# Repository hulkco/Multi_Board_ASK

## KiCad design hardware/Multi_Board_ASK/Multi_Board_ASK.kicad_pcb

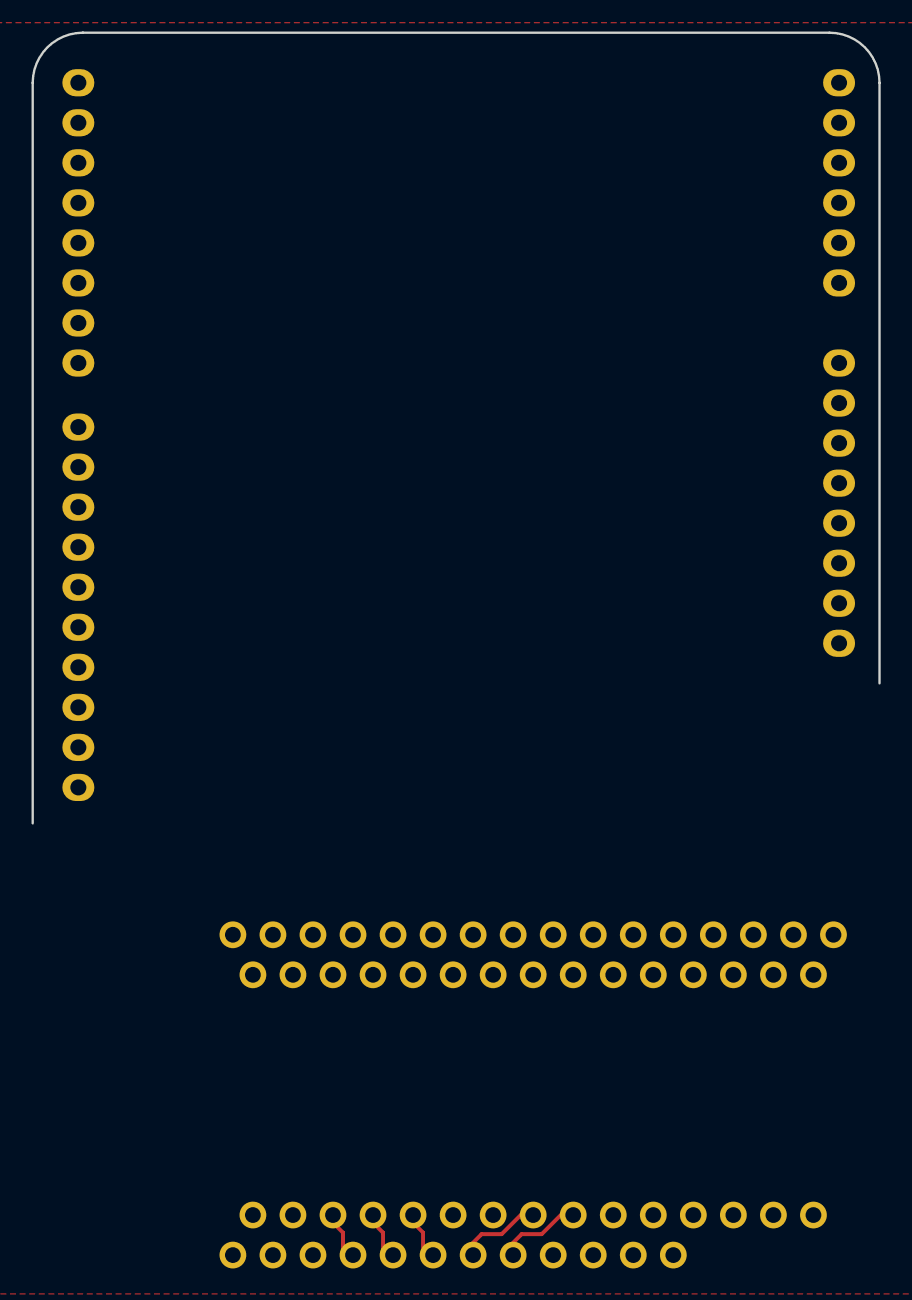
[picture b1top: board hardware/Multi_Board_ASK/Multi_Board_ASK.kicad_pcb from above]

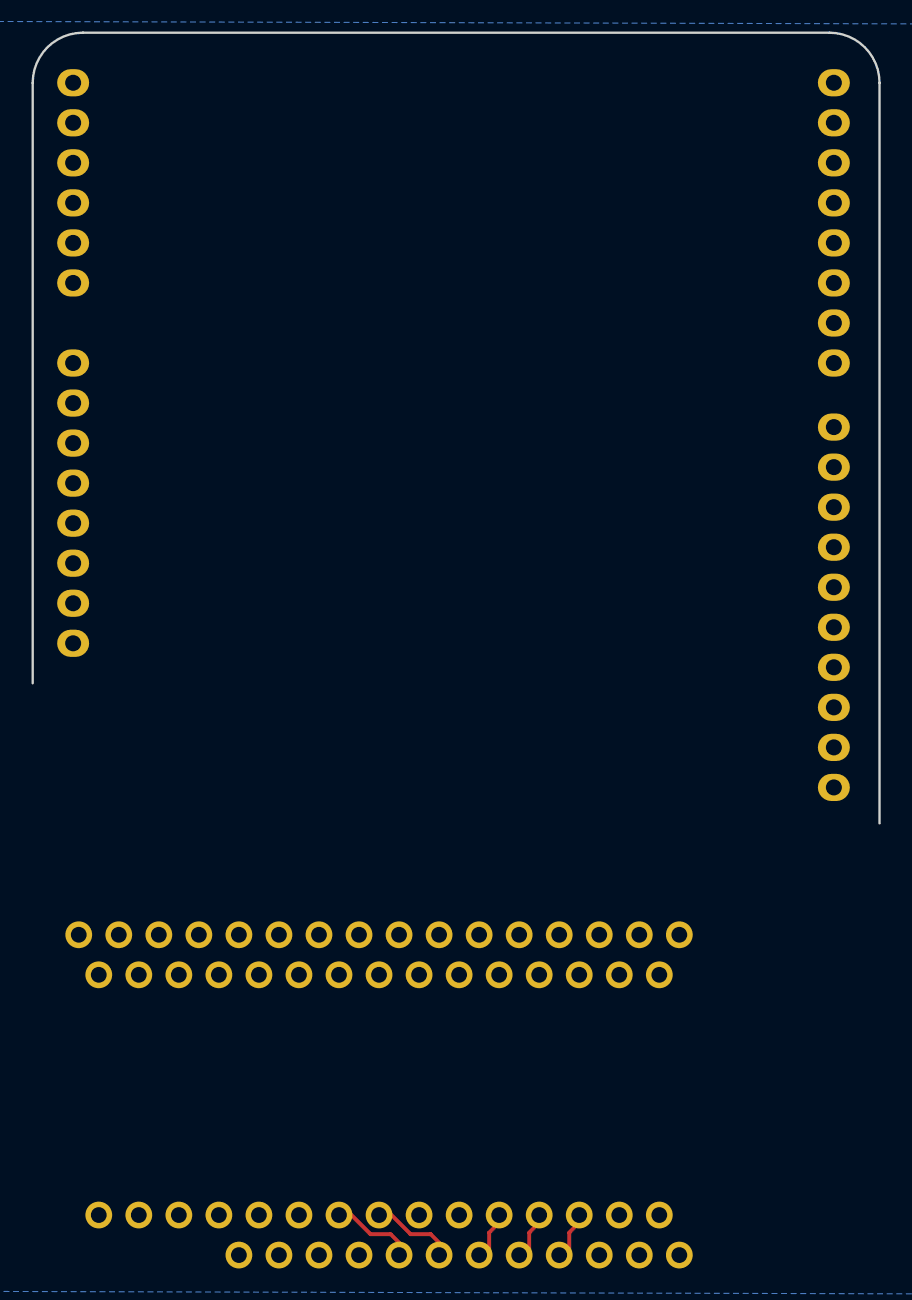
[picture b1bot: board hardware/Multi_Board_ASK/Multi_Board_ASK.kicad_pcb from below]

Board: 2 copper layers, 8 parts (2 on the bottom side), 27 nets.

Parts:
J1: feather long; PinHeader_1x16_P2.54mm_Vertical
J2: feather short; PinHeader_1x12_P2.54mm_Vertical
J3, J4: Conn_01x15; PinSocket_1x15_P2.54mm_Vertical
P1: Power; Socket_Strip_Arduino_1x08
P2: Analog; Socket_Strip_Arduino_1x06
P3: Digital; Socket_Strip_Arduino_1x10
P4: Digital; Socket_Strip_Arduino_1x08

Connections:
+3V3: J1.15, J4.14, P1.4
+5V: J2.10, J4.4, P1.5
/0(Rx): J1.3, J3.2, P4.8
/1(Tx): J1.2, J3.1, P4.7
/A0: J1.12, J4.12, P2.1
/A1: J1.11, J4.11, P2.2
/A2: J1.10, J4.10, P2.3
/A3: J1.9, J4.9, P2.4
/A6: J1.8, J4.6
/A7: J1.7, J4.5
/D2: J1.1, J3.5, P4.6
/D3(**): J2.3, J3.6, P4.5
/D4: J2.4, J3.7, P4.4
/D5(**): J2.5, J3.8, P4.3
/D6(**): J2.6, J3.9, P4.2
/D7: J3.10, P4.1
/D8: J2.7, J3.11, P3.10
/D9(**): J2.8, J3.12, P3.9
/D10(**): J2.9, J3.13, P3.8
/D11-MOSI: J1.5, J3.14, P3.7
/D12-MISO: J1.4, J3.15, P3.6
/D13-SCK: J1.6, J4.15, P3.5
/SCL-A5: J2.2, J4.7, P2.6, P3.1
/SDA-A4: J2.1, J4.8, P2.5, P3.2
/VIN: J2.12, J4.1, P1.8
/~RESET: J1.16, J3.3, J4.3, P1.3
GND: J1.13, J3.4, J4.2, P1.6, P1.7, P3.4

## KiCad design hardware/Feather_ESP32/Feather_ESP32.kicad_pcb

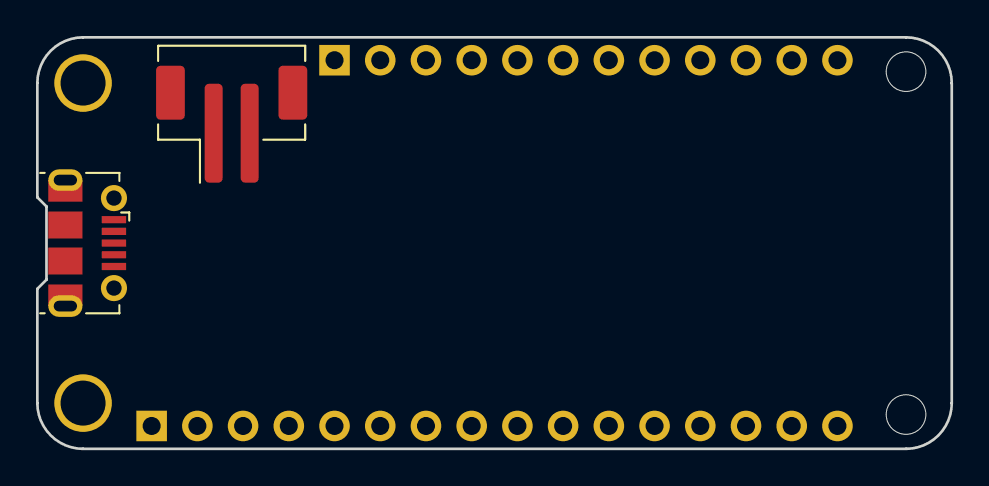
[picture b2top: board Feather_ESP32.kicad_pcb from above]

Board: 2 copper layers, 50.8 x 22.9 mm, 4 parts (0 on the bottom side), 3 nets, no tracks yet.

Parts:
J1: Conn_Battery; JST_PH_B2B-PH-SM4-TB_1x02-1MP_P2.00mm_Vertical
J2: USB_B_Micro; USB_Micro-B_Molex-105017-0001
J3: Conn_Left; PinSocket_1x16_P2.54mm_Vertical
J4: Conn_Right; PinSocket_1x12_P2.54mm_Vertical

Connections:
+BATT: J1.2, J4.1
GND: J1.1, J2.5, J2.6, J3.4
VBUS: J2.1, J4.3

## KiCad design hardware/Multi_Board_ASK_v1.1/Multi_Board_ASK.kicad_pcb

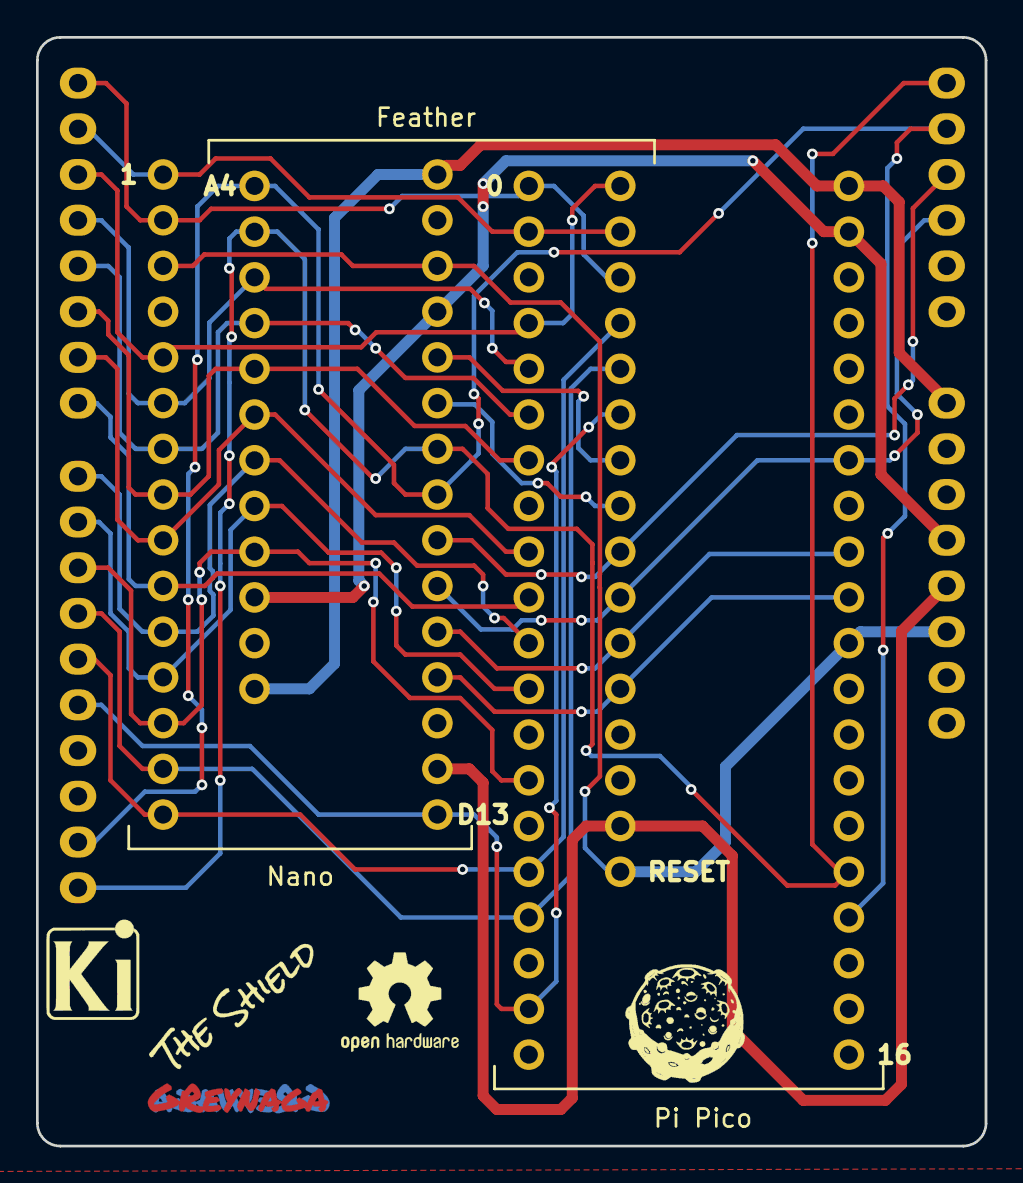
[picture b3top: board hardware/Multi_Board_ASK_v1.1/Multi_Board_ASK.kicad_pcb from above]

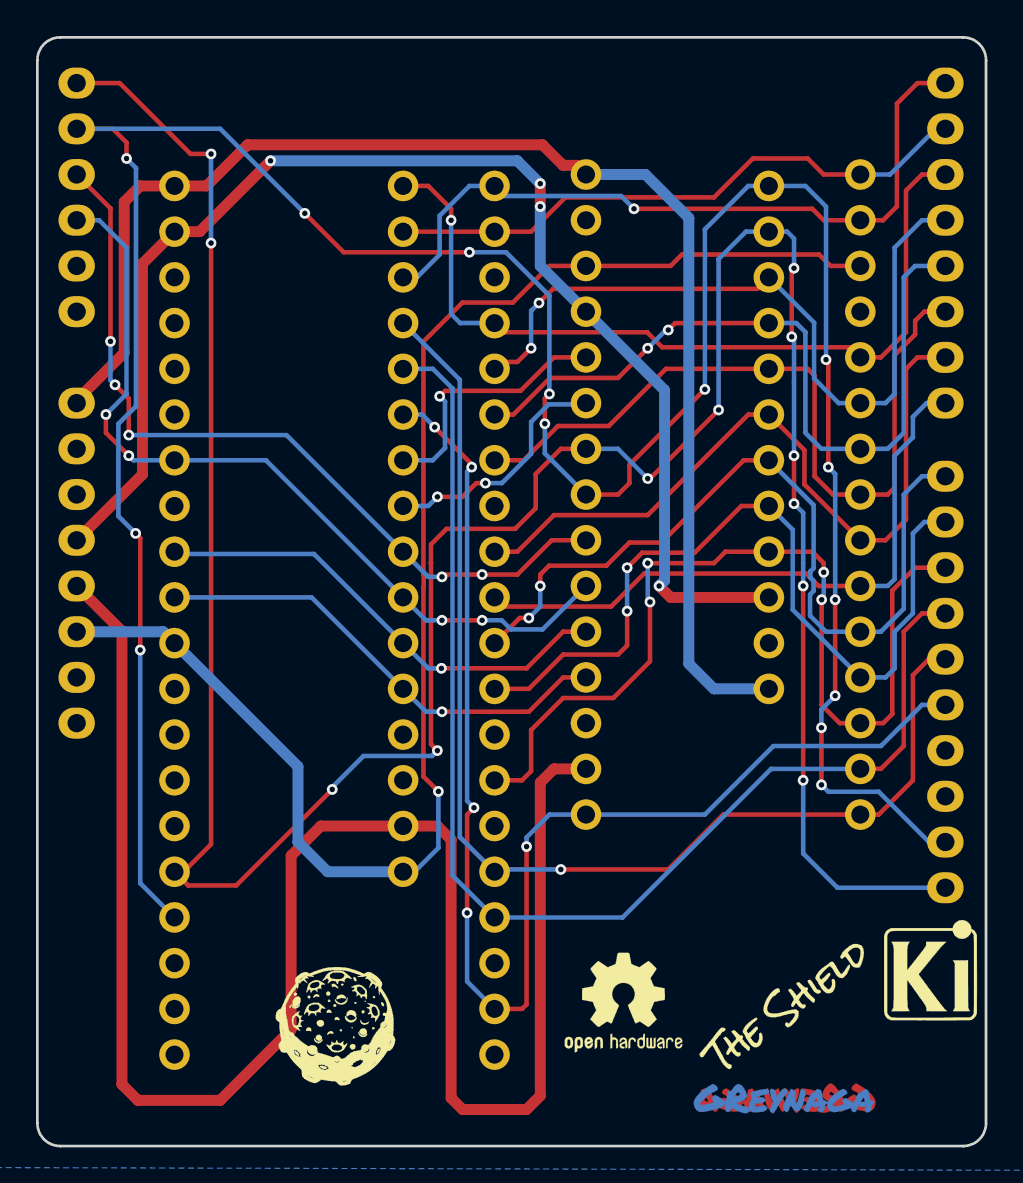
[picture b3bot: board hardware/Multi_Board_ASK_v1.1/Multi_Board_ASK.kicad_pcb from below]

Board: 2 copper layers, 52.7 x 61.6 mm, 20 parts (5 on the bottom side), 27 nets.

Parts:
J1: feather long; PinSocket_1x16_P2.54mm_Vertical
J2: feather short; PinSocket_1x12_P2.54mm_Vertical
J3: Nano 2; PinSocket_1x15_P2.54mm_Vertical
J4: Nano 1; PinSocket_1x15_P2.54mm_Vertical
J5: Pico 1; PinSocket_1x20_P2.54mm_Vertical
J6: Pico 2; PinSocket_1x20_P2.54mm_Vertical
P1: Power; Socket_Strip_Arduino_1x08
P2: Analog; Socket_Strip_Arduino_1x06
P3: Digital; Socket_Strip_Arduino_1x10
P4: Digital; Socket_Strip_Arduino_1x08
U1, U7: Feather_Cu; Feather_CU
U3, U8: KiCadLogo; Ki-2500
U4, U9: Moon_Firma; Moon_Firma_SilkS
U5, U10: Feather_Silks; Moon_The_Shield_SilkS
U6, U11: KiCadLogo; OSHW-Logo2_7.3x6mm_SilkScreen

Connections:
+3V3: J1.15, J4.14, J6.5, P1.4
+5V: J2.10, J4.4, J6.2, P1.5
/0(Rx): J1.3, J3.2, J5.1, P4.8
/1(Tx): J1.2, J3.1, J5.2, P4.7
/A0: J1.12, J4.12, J6.10, P2.1
/A1: J1.11, J4.11, J6.9, P2.2
/A2: J1.10, J4.10, J6.7, P2.3
/A3: J1.9, J4.9, P2.4
/A6: J1.8, J4.6
/A7: J1.7, J4.5
/D2: J1.1, J3.5, J5.4, P4.6
/D3(**): J2.3, J3.6, J5.5, P4.5
/D4: J2.4, J3.7, J5.6, P4.4
/D5(**): J2.5, J3.8, J5.7, P4.3
/D6(**): J2.6, J3.9, J5.9, P4.2
/D7: J3.10, J5.10, P4.1
/D8: J2.7, J3.11, J5.11, P3.10
/D9(**): J2.8, J3.12, J5.12, P3.9
/D10(**): J2.9, J3.13, J5.14, P3.8
/D11-MOSI: J1.5, J3.14, J5.17, P3.7
/D12-MISO: J1.4, J3.15, J5.16, P3.6
/D13-SCK: J1.6, J4.15, J5.19, P3.5
/SCL-A5: J2.2, J4.7, J6.16, P2.6, P3.1
/SDA-A4: J2.1, J4.8, J6.17, P2.5, P3.2
/VIN: J2.12, J4.1, J6.1, P1.8
/~RESET: J1.16, J3.3, J4.3, J6.11, P1.3
GND: J1.13, J3.4, J4.2, J5.3, J5.8, J5.13, J5.18, J6.3, J6.8, J6.13, J6.18, P1.6, P1.7, P3.4

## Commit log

2021-04-08 Add gitignore
2021-04-08 Firts files add
2021-04-08 Update gitignore
2021-04-08 minors
2021-05-13 Add doctos
2021-05-16 Add route tracks & 3dModels
2021-05-16 Some changes
